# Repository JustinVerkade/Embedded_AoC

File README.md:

# Embedded_AoC
## Introduction
The days are flying and the time is nearly due, to help Santa with his IT problems are you helping him too?

From the 1st to the 25th of december it his time to step up, but a man of this age requires a little bit of backup. He needs our assistance in his time of need to bring happiness and joy, so he can gift everyone a little toy. All systems online and ready to party, and you will always see that everything at the moment of truth, turns naughty.

To ensure christmass is a success I will provide backup on the fly, but his sleigh is limited in power and not equiped with wi-fi. Hardware needs to be compact and not weight down his sleigh, hence why it does not even have a display.

May my engineering prowes create machinery capable of this mission in this years Advent of Code edition.

### Real introduction
As embedded software developer my work generaly constraints me on available processing power and memory requiring carefull programming. As part of my self study I like doing software puzzles and designing hardware so 1 is 1 and so we have a custom PCB for AoC.

My main goals for this project is designing faster hardware and getting the external memory to work at proper speeds. The second part of these goals is to solve all the puzzles using the limited power and memory.

## Hardware

    Processor:      
        Model:  STM32H533ZET6
        Clock:  0.25 GHz
        Flash:  512kB
        Memory: 272kB(RAM) + 8MB(SRAM)

    Peripherals:
        USB-FS
        RGB status LED
        Piezo buzzer
        Reset button
        User button
        Arrow buttons

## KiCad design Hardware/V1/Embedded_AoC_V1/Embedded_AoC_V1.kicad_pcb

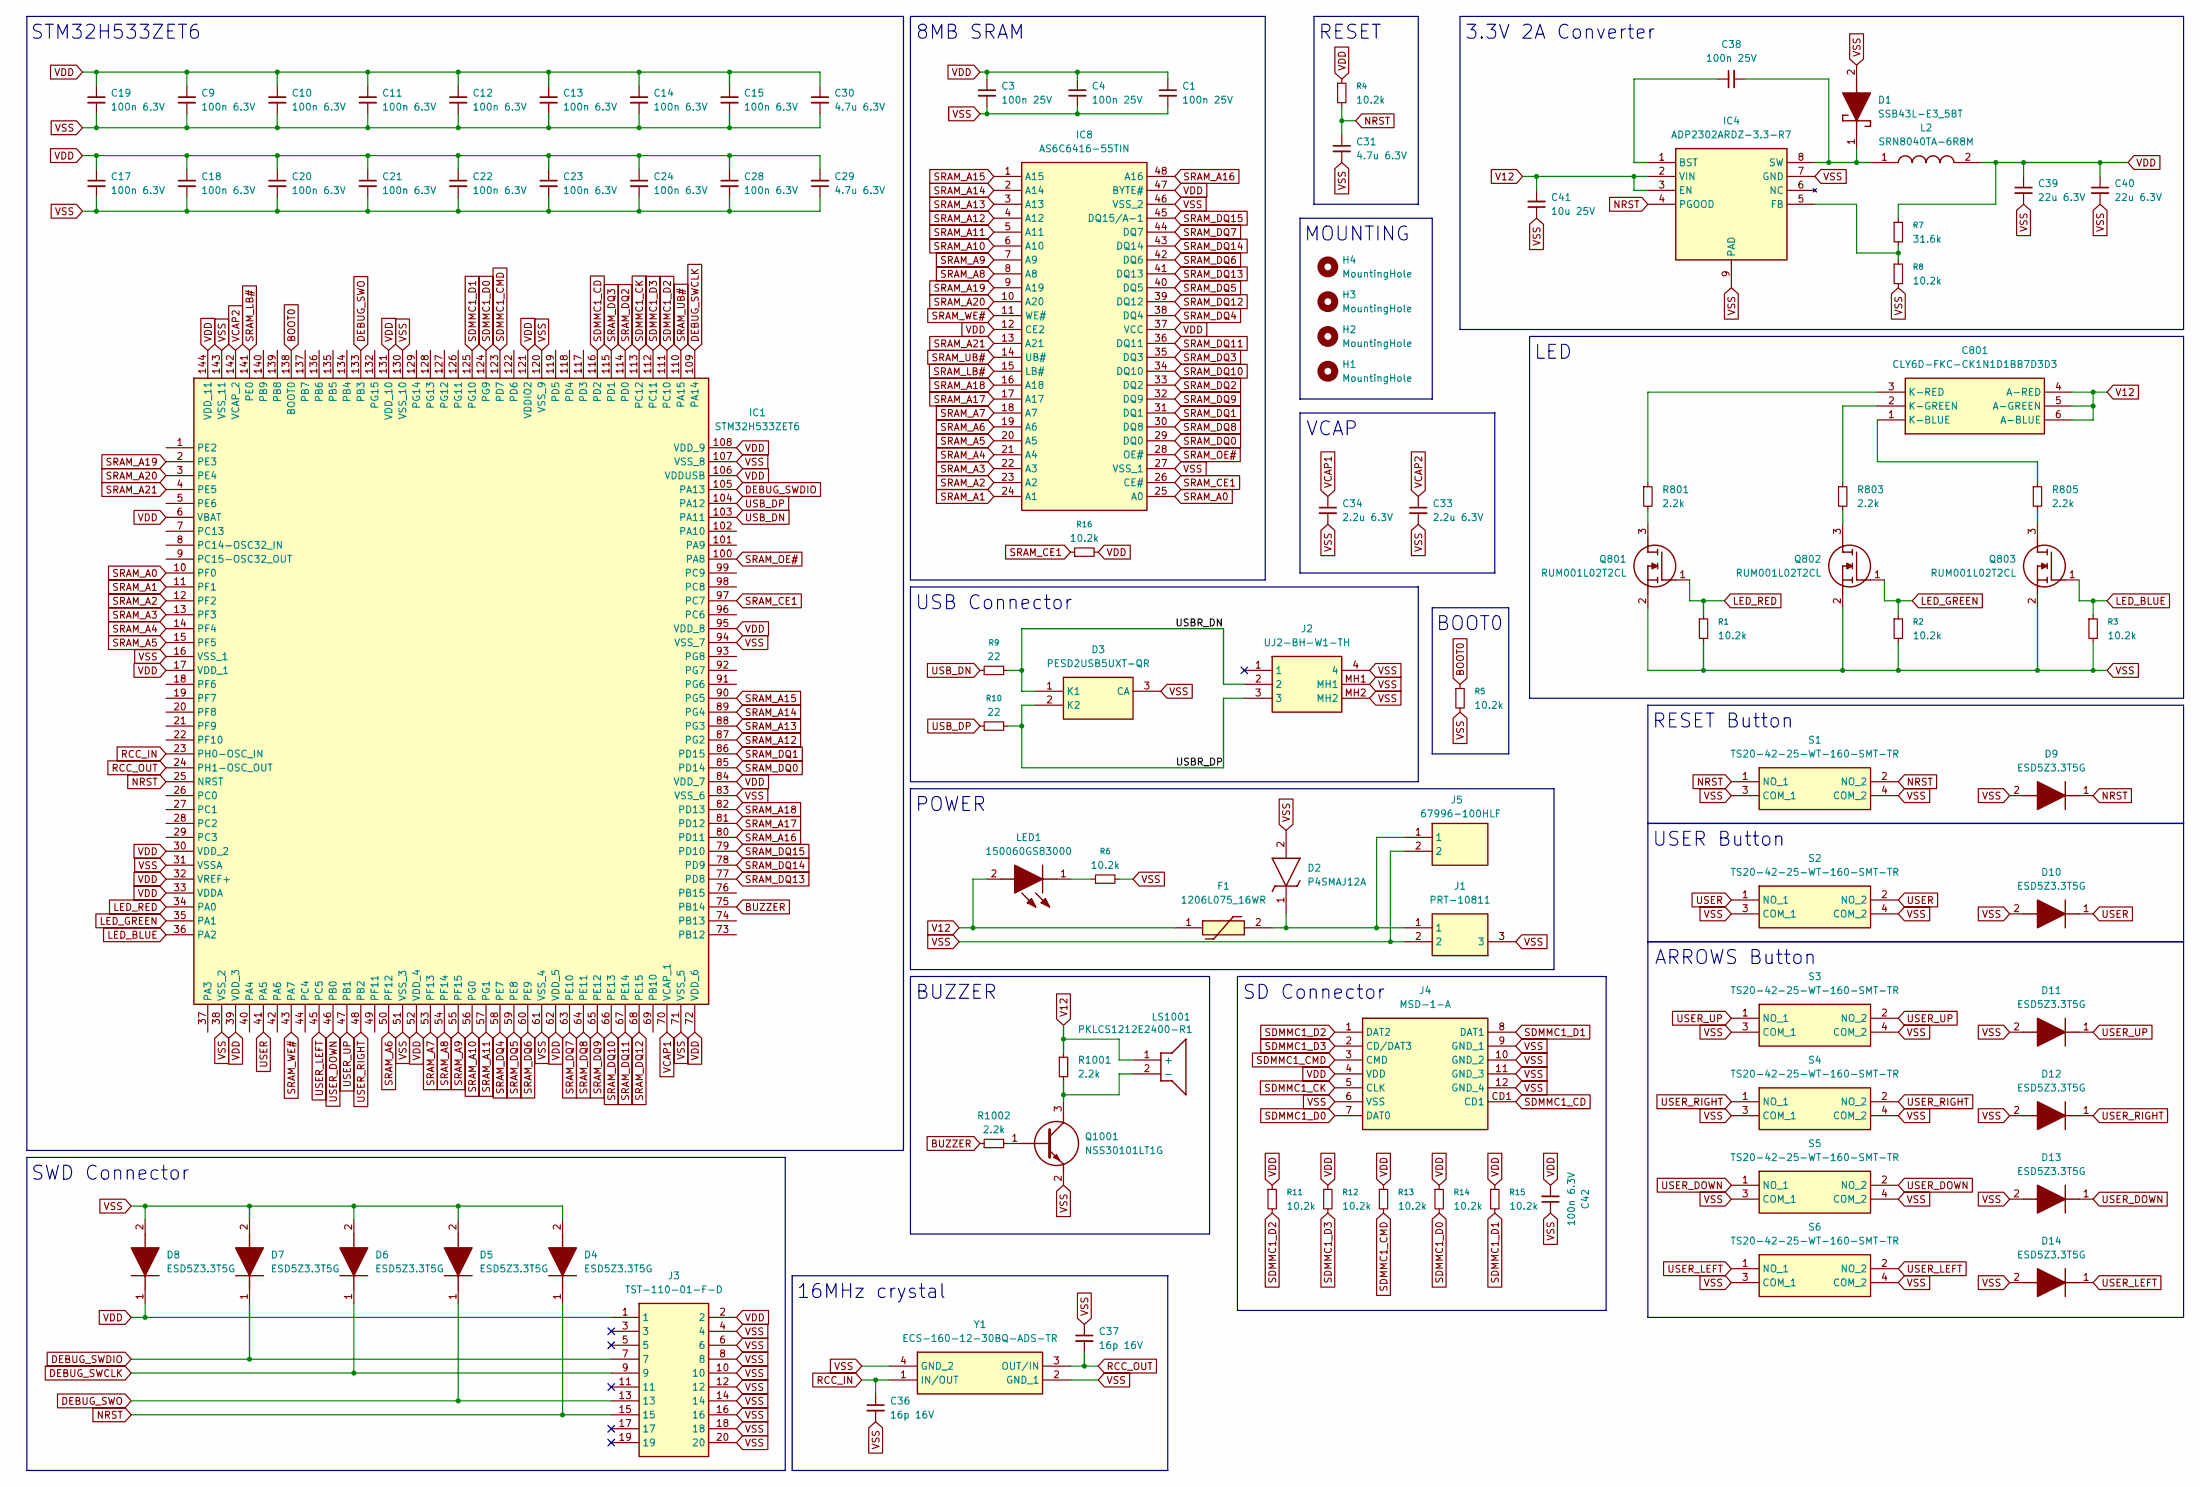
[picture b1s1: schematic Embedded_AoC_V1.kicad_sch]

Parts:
C1, C3, C4, C38: 100n 25V; C_0402_1005Metric
C9, C10, C11, C12, C13, C14, C15, C17, C18, C19, C20, C21, C22, C23, C24, C28, C42: 100n 6.3V; C_0402_1005Metric
C29, C30, C31: 4.7u 6.3V; C_0603_1608Metric
C33, C34: 2.2u 6.3V; C_0603_1608Metric
C36, C37: 16p 16V; C_0402_1005Metric
C39, C40: 22u 6.3V; C_1206_3216Metric
C41: 10u 25V; C_0805_2012Metric
C801: CLY6D-FKC-CK1N1D1BB7D3D3; PLCC6; Mouser Part Number 941-CLY6DFKCCK1N1D1B
D1: SSB43L-E3_5BT; SSB43LE35BT; Mouser Part Number 625-SSB43L-E3/5BT
D2: P4SMAJ12A; DIOM5027X240N; Manufacturer_Part_Number P4SMAJ12A
D3: PESD2USB5UXT-QR; SOT95P230X110-3N; Mouser Part Number 771-PESD2USB5UXT-QR
D4, D5, D6, D7, D8, D9, D10, D11, D12, D13, D14: ESD5Z3.3T5G; SODFL1608X70N; Mouser Part Number 863-ESD5Z3.3T5G
F1: 1206L075_16WR; 1206L075132WR; Mouser Part Number 576-1206L075/16WR
H1, H2, H3, H4: MountingHole; MountingHole_3.2mm_M3_Pad_Via
IC1: STM32H533ZET6; QFP50P2200X2200X160-144N; Mouser Part Number 511-STM32H533ZET6
IC4: ADP2302ARDZ-3.3-R7; SOIC127P600X175-9N; Mouser Part Number 584-ADP2302ARDZ3.3R7
IC8: AS6C6416-55TIN; SOP50P2000X120-48N; Mouser Part Number 913-AS6C6416-55TIN
J1: PRT-10811; PRT10811; Mouser Part Number 474-PRT-10811
J2: UJ2-BH-W1-TH; UJ2BHW1TH; Mouser Part Number 490-UJ2-BH-W1-TH
J3: TST-110-01-F-D; TST-110-XX-Y-D; Mouser Part Number 200-TST11001FD
J4: MSD-1-A; MSD1A; Mouser Part Number 179-MSD-1-A
J5: 67996-100HLF; HDRV2W67P254_2X1_254X483X858P; Manufacturer_Part_Number 67996-100HLF
L2: SRN8040TA-6R8M; INDPM8080X450N; Mouser Part Number 652-SRN8040TA-6R8M
LED1: 150060GS83000; LEDC1608X115N; Manufacturer_Part_Number 150060GS83000
LS1001: PKLCS1212E2400-R1; PKLCS1212E2400R1; Mouser Part Number 81-PKLCS1212E2400-R1
Q801, Q802, Q803: RUM001L02T2CL; SOT723; Mouser Part Number 755-RUM001L02T2CL
Q1001: NSS30101LT1G; SOT96P237X111-3N; Mouser Part Number 863-NSS30101LT1G
R1, R2, R3, R4, R5, R6, R8, R11, R12, R13, R14, R15, R16: 10.2k; R_0402_1005Metric
R7: 31.6k; R_0402_1005Metric
R9, R10: 22; R_0402_1005Metric
R801, R803, R805, R1001, R1002: 2.2k; R_0402_1005Metric
S1, S2, S3, S4, S5, S6: TS20-42-25-WT-160-SMT-TR; TS204225WT160SMTTR; Mouser Part Number 179-TS204225WT160SMT
Y1: ECS-160-12-30BQ-ADS-TR; ECS1602030BDUTR; Mouser Part Number 520-160-12-30BQ-ADST

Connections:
/USBR_DN: D3.1 (K1), J2.2, R9.2
/USBR_DP: D3.2 (K2), J2.3, R10.2
BOOT0: IC1.138 (BOOT0), R5.1
BUZZER: IC1.75 (PB14), R1002.1
DEBUG_SWCLK: D6.1 (K), IC1.109 (PA14), J3.9
DEBUG_SWDIO: D7.1 (K), IC1.105 (PA13), J3.7
DEBUG_SWO: D5.1 (K), IC1.133 (PB3), J3.13
LED_BLUE: IC1.36 (PA2), Q803.1 (G), R3.1
LED_GREEN: IC1.35 (PA1), Q802.1 (G), R2.1
LED_RED: IC1.34 (PA0), Q801.1 (G), R1.1
NRST: C31.1, D4.1 (K), D9.1 (K), IC1.25 (NRST), IC4.4 (PGOOD), J3.15, R4.2, S1.1 (NO_1), S1.2 (NO_2)
unnamed: C801.1 (K-BLUE), R805.1
unnamed: C801.2 (K-GREEN), R803.1
unnamed: C801.3 (K-RED), R801.1
unnamed: C38.2, D1.1 (K), IC4.8 (SW), L2.1
unnamed: D2.1 (K), F1.2, J1.1, J5.1
unnamed: C38.1, IC4.1 (BST)
unnamed: IC4.5 (FB), R7.2, R8.1
unnamed: LED1.1 (K), R6.1
unnamed: LS1001.2 (-), Q1001.3 (C), R1001.2
unnamed: Q801.3 (D), R801.2
unnamed: Q802.3 (D), R803.2
unnamed: Q803.3 (D), R805.2
unnamed: Q1001.1 (B), R1002.2
RCC_IN: C36.1, IC1.23 (PH0-OSC_IN), Y1.1 (IN/OUT)
RCC_OUT: C37.2, IC1.24 (PH1-OSC_OUT), Y1.3 (OUT/IN)
SDMMC1_CD: IC1.116 (PD2), J4.CD1
SDMMC1_CK: IC1.113 (PC12), J4.5 (CLK)
SDMMC1_CMD: IC1.123 (PD7), J4.3 (CMD), R13.2
SDMMC1_D0: IC1.124 (PG9), J4.7 (DAT0), R14.2
SDMMC1_D1: IC1.125 (PG10), J4.8 (DAT1), R15.2
SDMMC1_D2: IC1.111 (PC10), J4.1 (DAT2), R11.2
SDMMC1_D3: IC1.112 (PC11), J4.2 (CD/DAT3), R12.2
SRAM_A0: IC1.10 (PF0), IC8.25 (A0)
SRAM_A1: IC1.11 (PF1), IC8.24 (A1)
SRAM_A2: IC1.12 (PF2), IC8.23 (A2)
SRAM_A3: IC1.13 (PF3), IC8.22 (A3)
SRAM_A4: IC1.14 (PF4), IC8.21 (A4)
SRAM_A5: IC1.15 (PF5), IC8.20 (A5)
SRAM_A6: IC1.50 (PF12), IC8.19 (A6)
SRAM_A7: IC1.53 (PF13), IC8.18 (A7)
SRAM_A8: IC1.54 (PF14), IC8.8 (A8)
SRAM_A9: IC1.55 (PF15), IC8.7 (A9)
SRAM_A10: IC1.56 (PG0), IC8.6 (A10)
SRAM_A11: IC1.57 (PG1), IC8.5 (A11)
SRAM_A12: IC1.87 (PG2), IC8.4 (A12)
SRAM_A13: IC1.88 (PG3), IC8.3 (A13)
SRAM_A14: IC1.89 (PG4), IC8.2 (A14)
SRAM_A15: IC1.90 (PG5), IC8.1 (A15)
SRAM_A16: IC1.80 (PD11), IC8.48 (A16)
SRAM_A17: IC1.81 (PD12), IC8.17 (A17)
SRAM_A18: IC1.82 (PD13), IC8.16 (A18)
SRAM_A19: IC1.2 (PE3), IC8.9 (A19)
SRAM_A20: IC1.3 (PE4), IC8.10 (A20)
SRAM_A21: IC1.4 (PE5), IC8.13 (A21)
SRAM_CE1: IC1.97 (PC7), IC8.26 (CE#), R16.1
SRAM_DQ0: IC1.85 (PD14), IC8.29 (DQ0)
SRAM_DQ1: IC1.86 (PD15), IC8.31 (DQ1)
SRAM_DQ2: IC1.114 (PD0), IC8.33 (DQ2)
SRAM_DQ3: IC1.115 (PD1), IC8.35 (DQ3)
SRAM_DQ4: IC1.58 (PE7), IC8.38 (DQ4)
SRAM_DQ5: IC1.59 (PE8), IC8.40 (DQ5)
SRAM_DQ6: IC1.60 (PE9), IC8.42 (DQ6)
SRAM_DQ7: IC1.63 (PE10), IC8.44 (DQ7)
SRAM_DQ8: IC1.64 (PE11), IC8.30 (DQ8)
SRAM_DQ9: IC1.65 (PE12), IC8.32 (DQ9)
SRAM_DQ10: IC1.66 (PE13), IC8.34 (DQ10)
SRAM_DQ11: IC1.67 (PE14), IC8.36 (DQ11)
SRAM_DQ12: IC1.68 (PE15), IC8.39 (DQ12)
SRAM_DQ13: IC1.77 (PD8), IC8.41 (DQ13)
SRAM_DQ14: IC1.78 (PD9), IC8.43 (DQ14)
SRAM_DQ15: IC1.79 (PD10), IC8.45 (DQ15/A-1)
SRAM_LB#: IC1.141 (PE0), IC8.15 (LB#)
SRAM_OE#: IC1.100 (PA8), IC8.28 (OE#)
SRAM_UB#: IC1.110 (PA15), IC8.14 (UB#)
SRAM_WE#: IC1.43 (PA7), IC8.11 (WE#)
USB_DN: IC1.103 (PA11), R9.1
USB_DP: IC1.104 (PA12), R10.1
USER: D10.1 (K), IC1.41 (PA5), S2.1 (NO_1), S2.2 (NO_2)
USER_DOWN: D13.1 (K), IC1.46 (PB0), S5.1 (NO_1), S5.2 (NO_2)
USER_LEFT: D14.1 (K), IC1.45 (PC5), S6.1 (NO_1), S6.2 (NO_2)
USER_RIGHT: D12.1 (K), IC1.48 (PB2), S4.1 (NO_1), S4.2 (NO_2)
USER_UP: D11.1 (K), IC1.47 (PB1), S3.1 (NO_1), S3.2 (NO_2)
V12: C41.2, C801.4 (A-RED), C801.5 (A-GREEN), C801.6 (A-BLUE), F1.1, IC4.2 (VIN), IC4.3 (EN), LED1.2 (A), LS1001.1 (+), R1001.1
VCAP1: C34.1, IC1.70 (VCAP_1)
VCAP2: C33.1, IC1.142 (VCAP_2)
VDD: C1.1, C3.1, C4.1, C9.1, C10.1, C11.1, C12.1, C13.1, C14.1, C15.1, C17.1, C18.1, C19.1, C20.1, C21.1, C22.1, C23.1, C24.1, C28.1, C29.2, C30.1, C39.1, C40.1, C42.2, D8.1 (K), IC1.6 (VBAT), IC1.17 (VDD_1), IC1.30 (VDD_2), IC1.32 (VREF+), IC1.33 (VDDA), IC1.39 (VDD_3), IC1.52 (VDD_4), IC1.62 (VDD_5), IC1.72 (VDD_6), IC1.84 (VDD_7), IC1.95 (VDD_8), IC1.106 (VDDUSB), IC1.108 (VDD_9), IC1.121 (VDDIO2), IC1.131 (VDD_10), IC1.144 (VDD_11), IC8.12 (CE2), IC8.37 (VCC), IC8.47 (BYTE#), J3.1, J3.2, J4.4 (VDD), L2.2, R4.1, R7.1, R11.1, R12.1, R13.1, R14.1, R15.1, R16.2
VSS: C1.2, C3.2, C4.2, C9.2, C10.2, C11.2, C12.2, C13.2, C14.2, C15.2, C17.2, C18.2, C19.2, C20.2, C21.2, C22.2, C23.2, C24.2, C28.2, C29.1, C30.2, C31.2, C33.2, C34.2, C36.2, C37.1, C39.2, C40.2, C41.1, C42.1, D1.2 (A), D2.2 (A), D3.3 (CA), D4.2 (A), D5.2 (A), D6.2 (A), D7.2 (A), D8.2 (A), D9.2 (A), D10.2 (A), D11.2 (A), D12.2 (A), D13.2 (A), D14.2 (A), IC1.16 (VSS_1), IC1.31 (VSSA), IC1.38 (VSS_2), IC1.51 (VSS_3), IC1.61 (VSS_4), IC1.71 (VSS_5), IC1.83 (VSS_6), IC1.94 (VSS_7), IC1.107 (VSS_8), IC1.120 (VSS_9), IC1.130 (VSS_10), IC1.143 (VSS_11), IC4.7 (GND), IC4.9 (PAD), IC8.27 (VSS_1), IC8.46 (VSS_2), J1.2, J1.3, J2.4, J2.MH1, J2.MH2, J3.4, J3.6, J3.8, J3.10, J3.12, J3.14, J3.16, J3.18, J3.20, J4.6 (VSS), J4.9 (GND_1), J4.10 (GND_2), J4.11 (GND_3), J4.12 (GND_4), J5.2, Q801.2 (S), Q802.2 (S), Q803.2 (S), Q1001.2 (E), R1.2, R2.2, R3.2, R5.2, R6.2, R8.2, S1.3 (COM_1), S1.4 (COM_2), S2.3 (COM_1), S2.4 (COM_2), S3.3 (COM_1), S3.4 (COM_2), S4.3 (COM_1), S4.4 (COM_2), S5.3 (COM_1), S5.4 (COM_2), S6.3 (COM_1), S6.4 (COM_2), Y1.2 (GND_1), Y1.4 (GND_2)

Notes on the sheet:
BUZZER
SD Connector
STM32H533ZET6
SWD Connector
BOOT0
3.3V 2A Converter
VCAP
8MB SRAM
USB Connector
MOUNTING
RESET
RESET Button
POWER
USER Button
LED
ARROWS Button
16MHz crystal

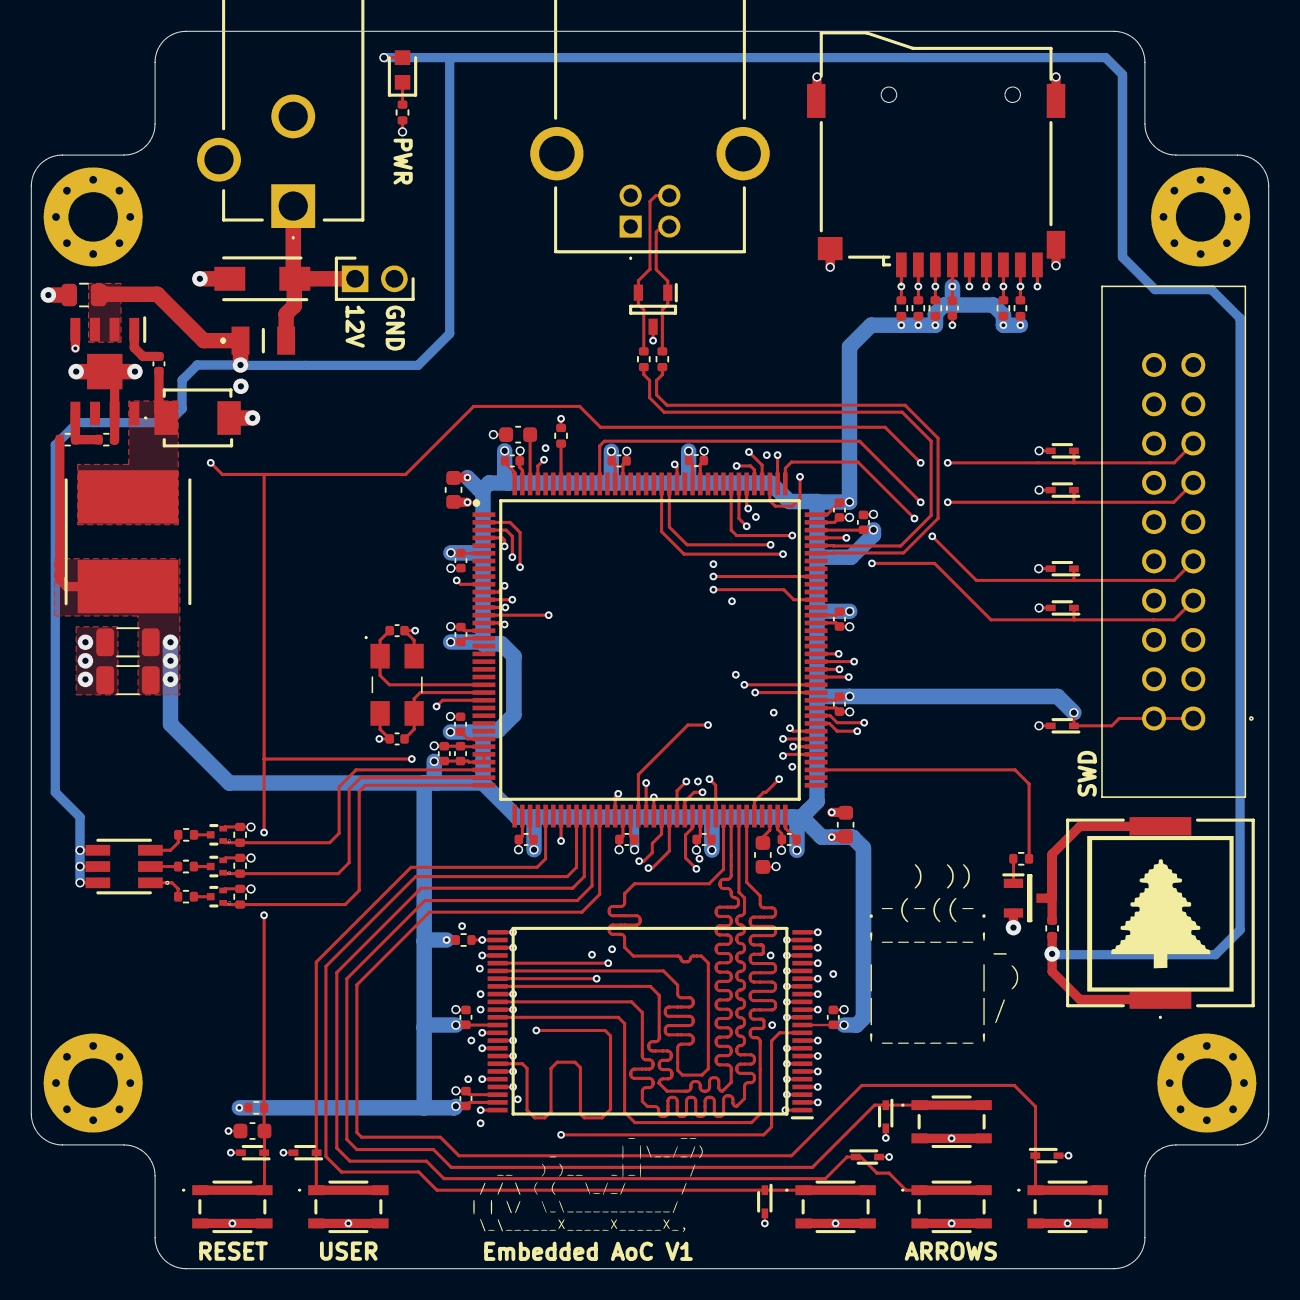
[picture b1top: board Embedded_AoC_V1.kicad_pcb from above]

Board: 6 copper layers, 80.0 x 80.0 mm, 94 parts (0 on the bottom side), 88 nets.

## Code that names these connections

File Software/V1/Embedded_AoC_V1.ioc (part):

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Mcu.Name=STM32H533ZETx
Mcu.Package=LQFP144
Mcu.UserName=STM32H533ZETx
PA0.GPIOParameters=GPIO_Label
PA0.GPIO_Label=LED_RED
PA0.Signal=S_TIM2_CH1
PA1.GPIOParameters=GPIO_Label
PA1.GPIO_Label=LED_GREEN
PA1.Signal=S_TIM2_CH2
PA11.Mode=Device
PA11.Signal=USB_DM
PA12.Mode=Device
PA12.Signal=USB_DP
PA13(JTMS/SWDIO).Mode=Trace_Asynchronous_SW
PA13(JTMS/SWDIO).Signal=DEBUG_JTMS-SWDIO
PA14(JTCK/SWCLK).Mode=Trace_Asynchronous_SW
PA14(JTCK/SWCLK).Signal=DEBUG_JTCK-SWCLK
PA15(JTDI).Signal=FMC_NBL1
PA2.GPIOParameters=GPIO_Label
PA2.GPIO_Label=LED_BLUE
PA2.Signal=S_TIM2_CH3
PA5.GPIOParameters=GPIO_PuPd,GPIO_Label
PA5.GPIO_Label=USER
PA5.GPIO_PuPd=GPIO_PULLUP
PA5.Signal=GPIO_Input
PA7.Signal=FMC_NWE
PA8.Signal=FMC_NOE
PB0.GPIOParameters=GPIO_PuPd,GPIO_Label
PB0.GPIO_Label=USER_DOWN
PB0.GPIO_PuPd=GPIO_PULLUP
PB0.Signal=GPIO_Input
PB1.GPIOParameters=GPIO_PuPd,GPIO_Label
PB1.GPIO_Label=USER_UP
PB1.GPIO_PuPd=GPIO_PULLUP
PB1.Signal=GPIO_Input
PB14.GPIOParameters=GPIO_Label
PB14.GPIO_Label=BUZZER
PB14.Signal=S_TIM12_CH1
PB2.GPIOParameters=GPIO_PuPd,GPIO_Label
PB2.GPIO_Label=USER_RIGHT
PB2.GPIO_PuPd=GPIO_PULLUP
PB2.Signal=GPIO_Input
PB3(JTDO/TRACESWO).Mode=Trace_Asynchronous_SW
PB3(JTDO/TRACESWO).Signal=DEBUG_JTDO-SWO
PC10.Mode=SD_4_bits_Wide_bus
PC10.Signal=SDMMC1_D2
PC11.Mode=SD_4_bits_Wide_bus
PC11.Signal=SDMMC1_D3
PC12.Mode=SD_4_bits_Wide_bus
PC12.Signal=SDMMC1_CK
PC5.GPIOParameters=GPIO_PuPd,GPIO_Label
PC5.GPIO_Label=USER_LEFT
PC5.GPIO_PuPd=GPIO_PULLUP
PC5.Signal=GPIO_Input
PC7.Mode=NorPsramChipSelect1_1
PC7.Signal=FMC_NE1
PD0.Signal=FMC_D2_DA2
PD1.Signal=FMC_D3_DA3
PD10.Signal=FMC_D15_DA15
PD11.Signal=FMC_A16_CLE
PD12.Signal=FMC_A17_ALE
PD13.Signal=FMC_A18
PD14.Signal=FMC_D0_DA0
PD15.Signal=FMC_D1_DA1
PD2.GPIOParameters=GPIO_PuPd,GPIO_Label
PD2.GPIO_Label=SDMMC1_CD
PD2.GPIO_PuPd=GPIO_PULLUP
PD2.Signal=GPIO_Input
PD7.Mode=SD_4_bits_Wide_bus
PD7.Signal=SDMMC1_CMD
PD8.Signal=FMC_D13_DA13
PD9.Signal=FMC_D14_DA14
PE0.Signal=FMC_NBL0
PE10.Signal=FMC_D7_DA7
PE11.Signal=FMC_D8_DA8
PE12.Signal=FMC_D9_DA9
PE13.Signal=FMC_D10_DA10
PE14.Signal=FMC_D11_DA11
PE15.Signal=FMC_D12_DA12
PE3.Signal=FMC_A19
PE4.Signal=FMC_A20
PE5.Signal=FMC_A21
PE7.Signal=FMC_D4_DA4
PE8.Signal=FMC_D5_DA5
PE9.Signal=FMC_D6_DA6
PF0.Signal=FMC_A0
PF1.Signal=FMC_A1
PF12.Signal=FMC_A6
PF13.Signal=FMC_A7
PF14.Signal=FMC_A8
PF15.Signal=FMC_A9
PF2.Signal=FMC_A2
PF3.Signal=FMC_A3
PF4.Signal=FMC_A4
PF5.Signal=FMC_A5
PG0.Signal=FMC_A10
PG1.Signal=FMC_A11
PG10.Mode=SD_4_bits_Wide_bus
PG10.Signal=SDMMC1_D1
PG2.Signal=FMC_A12
PG3.Signal=FMC_A13
PG4.Signal=FMC_A14
PG5.Signal=FMC_A15
PG9.Mode=SD_4_bits_Wide_bus
PG9.Signal=SDMMC1_D0
PH0-OSC_IN(PH0).Mode=HSE-External-Oscillator
PH0-OSC_IN(PH0).Signal=RCC_OSC_IN
PH1-OSC_OUT(PH1).Mode=HSE-External-Oscillator
PH1-OSC_OUT(PH1).Signal=RCC_OSC_OUT
RCC.HSE_VALUE=16000000
RCC.SYSCLKFreq_VALUE=250000000
RCC.SYSCLKSource=RCC_SYSCLKSOURCE_PLLCLK
board=custom

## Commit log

2025-08-13 First upload
2025-08-14 Added STM32 project and fixed pinning (USB DP/DN swapped)
2025-08-14 Released hardware
2025-08-14 Paranoiya commit to make sure latest stuff is saved
2025-08-15 PCBs are ordered and hardware folder is READ-ONLY
